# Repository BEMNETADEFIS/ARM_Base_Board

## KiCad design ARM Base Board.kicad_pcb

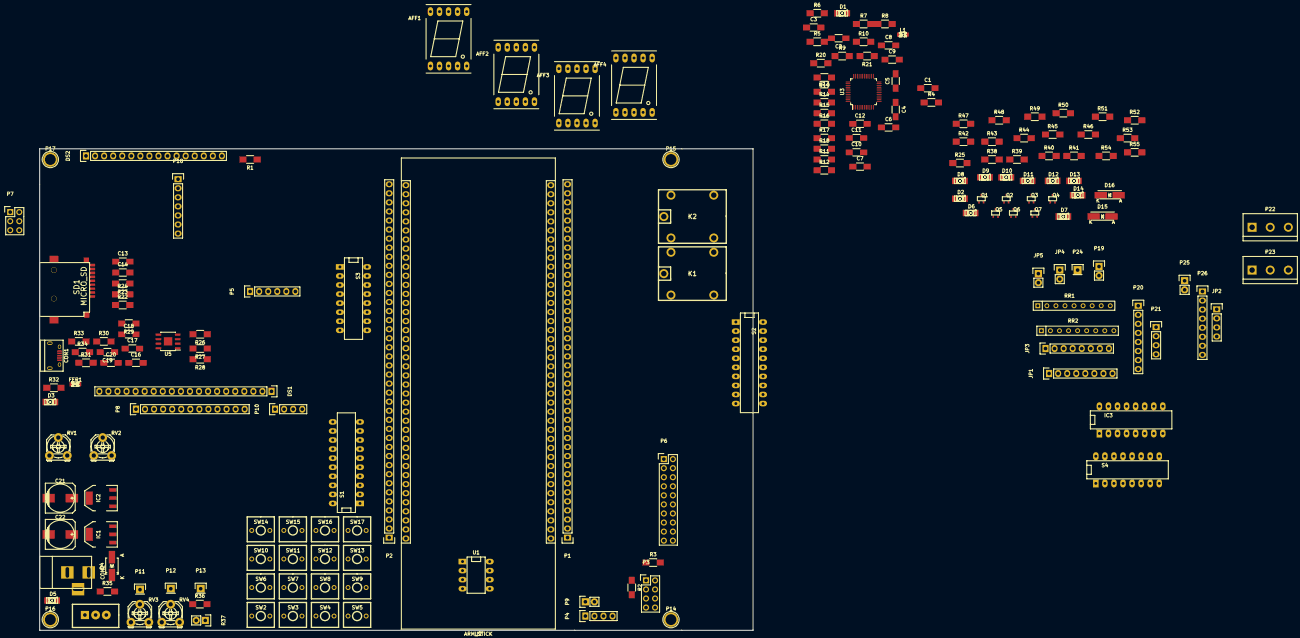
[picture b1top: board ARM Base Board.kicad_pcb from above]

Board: 2 copper layers, 200.0 x 135.0 mm, 177 parts (0 on the bottom side), 249 nets, no tracks yet.

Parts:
AFF1, AFF2, AFF3, AFF4: LTS-6960HR; 7SegmentLED_LTS6760_LTS6780
C1, C6, C18: 0.1uF; C_1206_HandSoldering
C2, C3, C7, C8, C9, C10, C12, C13, C16: 100nF; C_1206_HandSoldering
C4, C5: 8pF; C_1206_HandSoldering
C11, C14: 10uF; C_1206_HandSoldering
C17: 10uF/6.3V; C_1206_HandSoldering
C19, C20: 47pF; C_1206_HandSoldering
C21, C22: 100uF/25V; c_elec_8x10.5
CON1: USB A; USB_Micro-B
CON2: BARREL_JACK
D1, D2, D3, D6, D7, D8, D9, D10, D11, D12: LED; LED-1206_NEW
D4: 1n4148; Diode-SMA_Handsoldering
D5: PWR; LED-1206_NEW
D13: RL1; LED-1206_NEW
D14: RL2; LED-1206_NEW
D15, D16: 1N40XX; ZenerDiode_SMD
DS1: EE_RG12864j; Pin_Header_Straight_1x20
DS2: LCD-016N002L; Pin_Header_Straight_1x16
FER1: FERRITE; LED-0805
IC1, IC2: LM1117; SOT-223
IC3: L293D; DIP-16__300_ELL
JP1: MATRIX 4X4; Pin_Header_Straight_1x08
JP2: MOTAR CNTRL; Pin_Header_Straight_1x04
JP3: led array; Pin_Header_Straight_1x08
JP4, JP5: m1; Pin_Header_Straight_1x02
K1, K2: RELAYPTH; XL-RELAY-12
L1: INDUCTOR; LED-0805
P1, P2: CONN_01X40; Pin_Header_Straight_1x40
P3: CONN_4X2; Pin_Header_Straight_2x04
P4, P10: M4; Pin_Header_Straight_1x04
P5: M6; Pin_Header_Straight_1x06
P6: CONN_02X10; Pin_Header_Straight_2x10
P7: CONN_3X2; Pin_Header_Straight_2x03
P8: CONN_13; Pin_Header_Straight_1x13
P9, P19, P25: CONN_01X02; Pin_Header_Straight_1x02
P11, P12, P13: CONN_01X01; Pin_Header_Straight_1x01
P14, P15, P16, P17: CONN_01X01; 1pin
P18: CONN_01X07; Pin_Header_Straight_1x07
P20, P26: CONN_01X08; Pin_Header_Straight_1x08
P21: CONN_01X04; Pin_Header_Straight_1x04
P22, P23: CONN_01X03; bornier3
P24: CONN_1; Pin_Header_Straight_1x01
Q1, Q2, Q3, Q4, Q5, Q6, Q7: BC849; sc70
R1: 2.2k; R_1206_HandSoldering
R2, R4, R12, R26, R27, R28: 10K; R_1206_HandSoldering
R3: 47K; R_1206_HandSoldering
R5, R6, R10: 2K2; R_1206_HandSoldering
R7: 200E; R_1206_HandSoldering
R8, R9: 220E; R_1206_HandSoldering
R11, R13, R14, R15, R16, R17, R18, R30, R31: 33E; R_1206_HandSoldering
R19, R21: 4K87; R_1206_HandSoldering
R20: 1K5; R_1206_HandSoldering
R22, R45, R46, R48, R50, R51, R53, R55: 1K; R_1206_HandSoldering
R23, R24: 33K; R_1206_HandSoldering
R25, R38, R39, R40, R41, R42, R43, R44: 470; R_1206_HandSoldering
R29: 100K; R_1206_HandSoldering
R32, R35: 470E; R_1206_HandSoldering
R33, R34: 15K; R_1206_HandSoldering
R36: 10k; R_1206_HandSoldering
R37: Photores; Pin_Header_Straight_1x02
R47, R49, R52, R54: 68; R_1206_HandSoldering
RR1, RR2: RR8; r_pack8
RV1, RV2, RV3, RV4: POT; Potentiometer_Triwood_RM-065
S1: ETHERNET; DIP-20__300_ELL
S2: UART/SPI/I2C; DIP-20__300_ELL
S3: USB/SD/ETH; DIP-16__300_ELL
S4: SW_DIP-8; DIP-16__300_ELL
SD1: MICRO_SD; Micro_SD
SW1: Power; SPSPT_XL_NEW
SW2: C; SW_PUSH_SMALL_2pin_3D_xl
SW3: D; SW_PUSH_SMALL_2pin_3D_xl
SW4: E; SW_PUSH_SMALL_2pin_3D_xl
SW5: F; SW_PUSH_SMALL_2pin_3D_xl
SW6: 9; SW_PUSH_SMALL_2pin_3D_xl
SW7: 0; SW_PUSH_SMALL_2pin_3D_xl
SW8: A; SW_PUSH_SMALL_2pin_3D_xl
SW9: B; SW_PUSH_SMALL_2pin_3D_xl
SW10: 5; SW_PUSH_SMALL_2pin_3D_xl
SW11: 6; SW_PUSH_SMALL_2pin_3D_xl
SW12: 7; SW_PUSH_SMALL_2pin_3D_xl
SW13: 8; SW_PUSH_SMALL_2pin_3D_xl
SW14: 1; SW_PUSH_SMALL_2pin_3D_xl
SW15: 2; SW_PUSH_SMALL_2pin_3D_xl
SW16: 3; SW_PUSH_SMALL_2pin_3D_xl
SW17: 4; SW_PUSH_SMALL_2pin_3D_xl
U1: 24C256__EEPROM; DIP-8__300_ELL
U2: ARM_STICK; ARM_Stick
U3: DP83848; LQFP-48_7x7mm_Pitch0.5mm
U5: LM3526; SOIC-8-1EP_3.9x4.9mm_Pitch1.27mm

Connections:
9/12V: C21.1, IC1.3, IC3.8, SW1.2
+3.3VP: C13.1, C14.1, D4.1, D5.1, IC2.2, IC2.4, L1.1, P1.39, P3.1, P4.2, P5.2, R2.1, R3.1, R22.1, R23.2, R24.2, R26.1, R27.1, R28.1, R32.2, R36.1, RV3.1, RV4.1, SD1.4, U1.8, U2.39
+5V: C16.2, C22.1, D4.2, D15.2, D16.2, DS1.2, DS2.2, IC1.2, IC1.4, IC2.3, IC3.1, IC3.9, IC3.16, K1.5, K2.5, P2.39, P6.19, P18.3, Q5.3, R1.1, R47.2, R49.2, R52.2, R54.2, RR1.1, RR2.1, RV1.3, RV2.3, U2.42, U5.7
/7Segment,Relay,/DP: AFF1.5, AFF2.5, AFF3.5, AFF4.5, P20.1
/7Segment,Relay,/SG-1: AFF1.7, AFF2.7, AFF3.7, AFF4.7, P20.8
/7Segment,Relay,/SG-2: AFF1.6, AFF2.6, AFF3.6, AFF4.6, P20.7
/7Segment,Relay,/SG-3: AFF1.4, AFF2.4, AFF3.4, AFF4.4, P20.6
/7Segment,Relay,/SG-4: AFF1.2, AFF2.2, AFF3.2, AFF4.2, P20.5
/7Segment,Relay,/SG-5: AFF1.1, AFF2.1, AFF3.1, AFF4.1, P20.4
/7Segment,Relay,/SG-6: AFF1.9, AFF2.9, AFF3.9, AFF4.9, P20.3
/7Segment,Relay,/SG-7: AFF1.10, AFF2.10, AFF3.10, AFF4.10, P20.2
/46/USB_CONNECT: P2.35, U2.46
/57/VBUS: P2.24, U2.57
/60/USB_OVRCR: P2.21, S3.3, U2.60
/65/USB_PWRD: P2.16, S3.4, U2.65
/68/USB_PPWR: P2.13, S3.5, U2.68
/69/USB_UP_LED: P2.12, S3.6, U2.69
/70/ENET_MDIO: P2.11, S1.10, U2.70
/71/ENET_MDC: P2.10, S1.9, U2.71
/72/ENET_REF_CLK: P2.9, S1.8, U2.72
/73/ENET_RX_ER: P2.8, S1.7, U2.73
/75/ENET_RXD1: P2.6, S1.6, U2.75
/76/ENET_RXD0: P2.5, S1.5, U2.76
/77/ENET_CRS: P2.4, S1.4, U2.77
/78/ENET_TX_EN: P2.3, S1.3, U2.78
/79/ENET_TXD1: P2.2, S1.2, U2.79
/80/ENET_TXD0: P2.1, S1.1, U2.80
/ADC0: P1.21, U2.21
/ADC1: P1.22, U2.22
/ADC2: P1.23, U2.23
/ADC3: P1.24, U2.24
/ETH RESET: P2.37, S3.8, U2.44
/GPIO 10: P1.11, P6.18, U2.11
/GPIO 11: P1.12, P6.17, U2.12
/GPIO 12: P1.13, P6.16, U2.13
/GPIO 13: P1.14, P6.15, U2.14
/GPIO 14: P1.15, P6.14, U2.15
/GPIO 15: P1.16, P6.13, U2.16
/GPIO 16: P1.17, P6.12, U2.17
/GPIO 17: P1.18, P6.11, U2.18
/GPIO 18: P1.19, P6.10, U2.19
/GPIO 19: P1.20, P6.9, U2.20
/I2C_SCL: P1.26, P6.7, S2.9, U2.26
/I2C_SDA: P1.25, P6.8, S2.10, U2.25
/RS232/M1a: IC3.2, JP2.4
/RS232/M1b: IC3.7, JP2.3
/RS232/M1c: IC3.3, JP4.1
/RS232/M1d: IC3.6, JP4.2
/RS232/M2a: IC3.15, JP2.2
/RS232/M2b: IC3.10, JP2.1
/RS232/M2c: IC3.14, JP5.1
/RS232/M2d: IC3.11, JP5.2
/RXD0: P1.32, P6.1, S2.3, U2.32
/RXD1: P1.34, S2.1, U2.34
/SCL_EEPROM: S2.12, U1.6
/SDA_EEPROM: S2.11, U1.5
/SD_DETECT: P2.36, S3.7, U2.45
/SPI_MISO: P1.28, P6.5, S2.7, U2.28
/SPI_MOSI: P1.27, P6.6, S2.8, U2.27
/SPI_SCL: P1.29, P6.4, S2.6, U2.29
/SPI_SSEL: P1.30, P6.3, S2.5, U2.30
/TXD0: P1.31, P6.2, S2.4, U2.31
/TXD1: P1.33, S2.2, U2.33
/USB+_HOST: P1.36, S3.2, U2.36
/USB-_HOST: P1.35, S3.1, U2.35
/arm_base_ethernet/LED_ACT: R6.1, U3.26
/arm_base_ethernet/LED_LINK: R5.2, U3.28
/arm_base_ethernet/LED_SPEED: D1.2, R10.2, U3.27
/arm_base_ethernet/PFBOUT: C6.2, C10.1, C11.1, C12.1, U3.18, U3.23, U3.37
/arm_base_ethernet/RD+: C4.1, U3.14
/arm_base_ethernet/RD-: C4.2, U3.13
/arm_base_ethernet/TD+: C5.2, U3.17
/arm_base_ethernet/TD-: C5.1, U3.16
/arm_base_ethernet/Veth: C1.1, C2.2, C3.1, C7.1, C8.1, C9.1, L1.2, R4.1, R5.1, R7.1, R9.1, R10.1, R12.1, R19.1, R20.1, U3.22, U3.32, U3.48
D+_HOST: C20.1, R31.2, S3.15
D-_HOST: C19.1, R30.2, S3.16
ENET_CRS: R13.1, S1.17
ENET_MDC: S1.12, U3.31
ENET_MDIO: R20.2, S1.11, U3.30
ENET_REF_CLK: S1.13, U3.34
ENET_RXD0: R15.1, S1.16
ENET_RXD1: R16.1, S1.15
ENET_RX_ER: R14.1, S1.14
ENET_TXD0: R18.1, S1.20
ENET_TXD1: R11.1, S1.19
ENET_TX_EN: R17.1, S1.18
ETH_RST: S3.9, U3.29
GND: C1.2, C2.1, C3.2, C6.1, C7.2, C8.2, C9.2, C10.2, C11.2, C12.2, C13.2, C14.2, C16.1, C17.2, C18.2, C19.2, C20.2, C21.2, C22.2, CON1.4, CON2.2, CON2.3, D2.2, D6.2, D7.2, D8.2, D9.2, D10.2, D11.2, D12.2, DS1.1, DS1.17, DS1.20, DS2.1, DS2.16, FER1.2, IC1.1, IC2.1, IC3.4, IC3.5, IC3.12, IC3.13, P1.40, P2.40, P4.1, P5.1, P6.20, P18.1, P25.2, Q1.2, Q2.2, R21.2, R29.1, R33.2, R34.2, R35.1, R37.2, RV2.1, RV3.3, RV4.3, S4.9, S4.10, S4.11, S4.12, S4.13, S4.14, S4.15, S4.16, SD1.6, SD1.10, SD1.11, SD1.12, SD1.13, U1.1, U1.2, U1.3, U1.4, U1.7, U2.40, U2.41, U3.15, U3.19, U3.35, U3.36, U3.47, U5.6
unnamed: AFF1.3, Q3.2
unnamed: AFF2.3, Q4.2
unnamed: AFF3.3, Q6.2
unnamed: AFF4.3, Q7.2
unnamed: CON1.2, R30.1, R34.1
unnamed: CON1.3, R31.1, R33.1
unnamed: CON1.5, CON1.6, FER1.1
unnamed: CON2.1, SW1.1
unnamed: D1.1, R9.2
unnamed: D2.1, R25.2
unnamed: D3.1, R32.1
unnamed: D5.2, R35.2
unnamed: D6.1, R38.2
unnamed: D7.1, R39.2
unnamed: D8.1, R40.2
unnamed: D9.1, R41.2
unnamed: D10.1, R42.2
unnamed: D11.1, R43.2
unnamed: D12.1, R44.2
unnamed: D13.1, P19.2
unnamed: D13.2, R45.1
unnamed: D14.1, P19.1
unnamed: D14.2, R46.1
unnamed: D15.1, K1.1, Q1.3
unnamed: D16.1, K2.1, Q2.3
unnamed: DS1.3, RV1.2
unnamed: DS1.4, DS2.4, P8.13
unnamed: DS1.5, DS2.5, P8.12
unnamed: DS1.6, DS2.6, P8.11
unnamed: DS1.7, DS2.7, P8.10
unnamed: DS1.8, DS2.8, P8.9
unnamed: DS1.9, DS2.9, P8.8
unnamed: DS1.10, DS2.10, P8.7
unnamed: DS1.11, DS2.11, P8.6
unnamed: DS1.12, DS2.12, P8.5
unnamed: DS1.13, DS2.13, P8.4
unnamed: DS1.14, DS2.14, P8.3
unnamed: DS1.15, P8.2
unnamed: DS1.16, P8.1
unnamed: DS1.18, RV1.1
unnamed: DS1.19, DS2.15, R1.2
unnamed: DS2.3, RV2.2
unnamed: JP1.1, RR1.2, SW2.1, SW3.1, SW4.1, SW5.1
unnamed: JP1.2, RR1.3, SW6.1, SW7.1, SW8.1, SW9.1
unnamed: JP1.3, RR1.4, SW10.1, SW11.1, SW12.1, SW13.1
unnamed: JP1.4, RR1.5, SW14.1, SW15.1, SW16.1, SW17.1
unnamed: JP1.5, RR1.6, SW2.2, SW6.2, SW10.2, SW14.2
unnamed: JP1.6, RR1.7, SW3.2, SW7.2, SW11.2, SW15.2
unnamed: JP1.7, RR1.8, SW4.2, SW8.2, SW12.2, SW16.2
unnamed: JP1.8, RR1.9, SW5.2, SW9.2, SW13.2, SW17.2
unnamed: JP3.1, R44.1
unnamed: JP3.2, R43.1
unnamed: JP3.3, R42.1
unnamed: JP3.4, R41.1
unnamed: JP3.5, R40.1
unnamed: JP3.6, R39.1
unnamed: JP3.7, R38.1
unnamed: JP3.8, R25.1
unnamed: K1.2, P22.2
unnamed: K1.3, P22.3
unnamed: K1.4, P22.1
unnamed: K2.2, P23.2
unnamed: K2.3, P23.3
unnamed: K2.4, P23.1
unnamed: P1.1, U2.1
unnamed: P1.2, U2.2
unnamed: P1.3, U2.3
unnamed: P1.4, U2.4
unnamed: P1.5, U2.5
unnamed: P1.6, U2.6
unnamed: P1.7, U2.7
unnamed: P1.8, U2.8
unnamed: P1.9, U2.9
unnamed: P1.10, U2.10
unnamed: P2.7, U2.74
unnamed: P2.14, U2.67
unnamed: P2.15, U2.66
unnamed: P2.17, U2.64
unnamed: P2.18, U2.63
unnamed: P2.19, U2.62
unnamed: P2.20, U2.61
unnamed: P2.22, U2.59
unnamed: P2.23, U2.58
unnamed: P2.25, U2.56
unnamed: P2.26, U2.55
unnamed: P2.27, U2.54
unnamed: P2.28, U2.53
unnamed: P2.29, U2.52
unnamed: P2.30, U2.51
unnamed: P2.31, U2.50
unnamed: P2.32, U2.49
unnamed: P2.33, U2.48
unnamed: P2.34, U2.47
unnamed: P2.38, U2.43
unnamed: P3.3, R2.2
unnamed: P3.5, R3.2
unnamed: P4.3, P9.2
unnamed: P4.4, P9.1
unnamed: P5.6, P10.1
unnamed: P5.5, P10.2
unnamed: P5.4, P10.3
unnamed: P5.3, P10.4
unnamed: P11.1, RV3.2
unnamed: P12.1, RV4.2
unnamed: P13.1, R36.2, R37.1
unnamed: P21.1, R48.2
unnamed: P21.2, R51.2
unnamed: P21.3, R53.2
unnamed: P21.4, R55.2
unnamed: P24.1, R50.1
unnamed: P25.1, Q5.2
unnamed: P26.1, RR2.9, S4.8
unnamed: P26.2, RR2.8, S4.7
unnamed: P26.3, RR2.7, S4.6
unnamed: P26.4, RR2.6, S4.5
unnamed: P26.5, RR2.5, S4.4
unnamed: P26.6, RR2.4, S4.3
unnamed: P26.7, RR2.3, S4.2
unnamed: P26.8, RR2.2, S4.1
unnamed: Q1.1, R45.2
unnamed: Q2.1, R46.2
unnamed: Q3.1, R48.1
unnamed: Q3.3, R47.1
unnamed: Q4.1, R51.1
unnamed: Q4.3, R49.1
unnamed: Q5.1, R50.2
unnamed: Q6.1, R53.1
unnamed: Q6.3, R52.1
unnamed: Q7.1, R55.1
unnamed: Q7.3, R54.1
unnamed: R6.2, R8.2
unnamed: R11.2, U3.4
unnamed: R12.2, U3.7
unnamed: R13.2, U3.40
unnamed: R14.2, U3.41
unnamed: R15.2, U3.43
unnamed: R16.2, U3.44
unnamed: R17.2, U3.2
unnamed: R18.2, U3.3
unnamed: R19.2, U3.39
unnamed: R21.1, U3.24
unnamed: R23.1, SD1.8
unnamed: R24.1, SD1.1
unnamed: R26.2, U5.4
PRI_BLD: P1.37, P18.6, U2.37
RX: P7.3, P18.4
SD_CARD_DETECT: R22.2, S3.10, SD1.9
SPI_MISO_0: S2.14, SD1.7
SPI_MOSI_0: S2.13, SD1.3
SPI_SCK_0: S2.15, SD1.5
SPI_SSEL_0: S2.16, SD1.2
TX: P7.4, P18.5
UART_RXD0: P7.1, S2.18
UART_RXD1: P3.7, P7.5, S2.20
UART_TXD0: P7.2, S2.17
UART_TXD1: P3.2, P7.6, S2.19
USB_OVRCR: R28.2, S3.14, U5.2
USB_PPWR: R27.2, S3.12, U5.1
USB_PWRD: C17.1, C18.1, CON1.1, R29.2, S3.13, U5.8
USB_UP_LED: D3.2, S3.11
~RST: P1.38, P18.7, U2.38

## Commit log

2015-07-16 Added Files
